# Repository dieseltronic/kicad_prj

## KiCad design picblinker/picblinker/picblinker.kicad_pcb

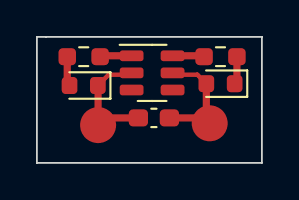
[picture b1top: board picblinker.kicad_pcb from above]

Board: 2 copper layers, 12.5 x 7.0 mm, 8 parts (0 on the bottom side), 6 nets.

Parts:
C1: 100nF; C_0603_1608Metric_Pad1.08x0.95mm_HandSolder
D1: rt; LED_0603_1608Metric
D2: gn; LED_0603_1608Metric
H1: Pad+; MountingHole_2.2mm_M2_DIN965_Pad_TopOnly
H2: Pad-; MountingHole_2.2mm_M2_DIN965_Pad_TopOnly
R1, R2: 560R; R_0603_1608Metric_Pad0.98x0.95mm_HandSolder
U1: PIC10F320-IOT; SOT-23-6

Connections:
unnamed: C1.1, D2.2 (A), H1.1, U1.5 (VDD)
unnamed: C1.2, D1.1 (K), H2.1, U1.2 (VSS)
unnamed: D1.2 (A), R2.1
unnamed: D2.1 (K), R1.1
unnamed: R2.2, U1.1 (RA0)
unnamed: R1.2, U1.6 (RA3)

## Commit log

2022-10-30 Add existing project files to Git
